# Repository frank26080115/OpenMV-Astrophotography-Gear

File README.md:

I made a Polar Scope and Autoguider using OpenMV. Both projects utilize OpenMV's embedded image processing algorithms to assist in astrophotography while using WiFi to provide a user interface on any smartphone.

A polar scope is a small telescope used to polar-align star-tracking camera mounts and equatorial telescope mounts. A digital camera version that leverages OpenMV computer vision algorithms can achieve much better accuracy, improving the quality of astro-photographs! With a WiFi connected web UI, it's way more convenient to use.

An autoguider is something that locks onto one star, and commands a computerized telescope mount to move in tiny steps to follow that one star, thus correcting for any errors in the gear train and polar alignment. This prevents blurriness in astrophotographs in extra long exposures.

OpenMV is an open source hardware platform that combines a camera, microcontroller, and image processing algorithms. It can run MicroPython and has accessories such as the WiFi shield. It is a quick and easy way to implement low power embedded vision processing in projects such as self-driving robot racecars.

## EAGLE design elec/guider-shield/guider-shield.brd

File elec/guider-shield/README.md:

This circuit schematic and PCB design is a variation of the OpenMV WiFi shield.

The original GitHub repo for the OpenMV WiFi shield is found at [https://github.com/openmv/openmv-boards/tree/master/shields/wifi](https://github.com/openmv/openmv-boards/tree/master/shields/wifi)

It allows for a bigger camera lens to be mounted. It also adds a ST-4 port in order to control telescope mounts.

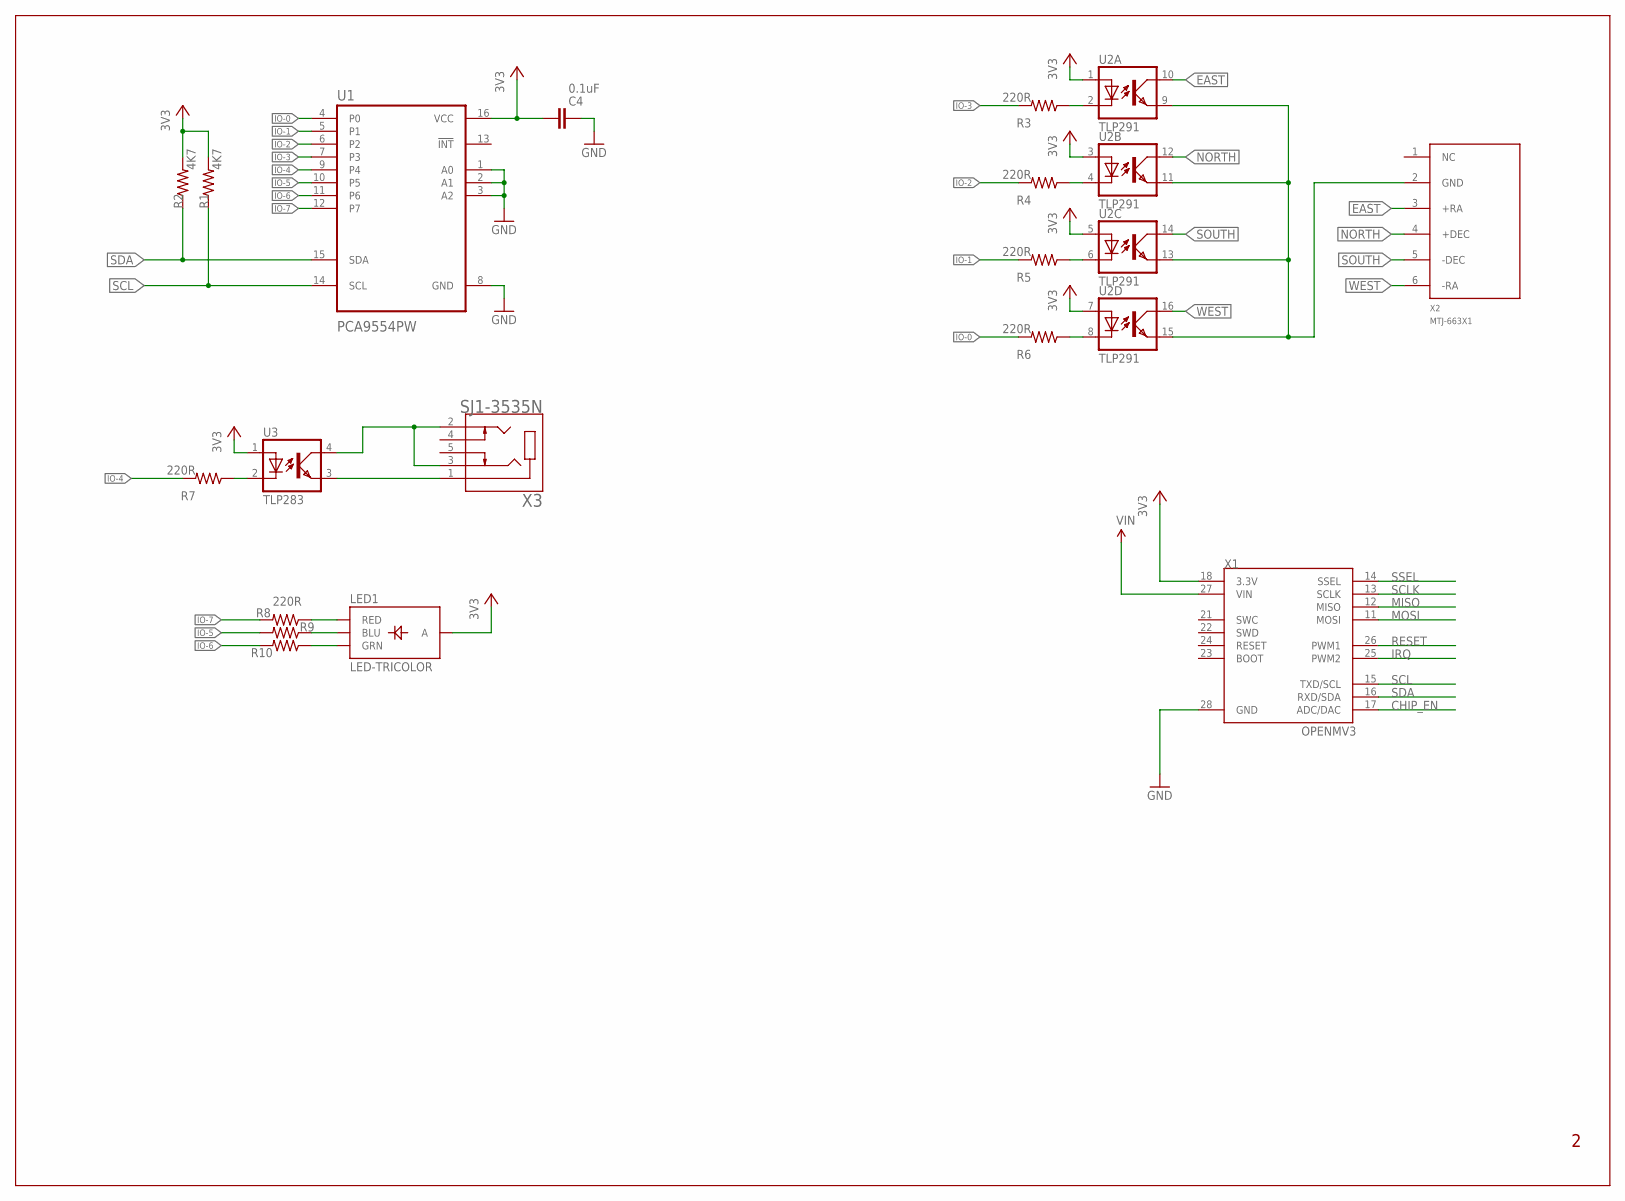
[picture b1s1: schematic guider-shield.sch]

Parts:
C4: 0.1uF; 0603-CAP
LED1: LED-TRICOLOR; LED-TRICOLOR-SMD
R1, R2: 4K7; 0603-RES
R3, R4, R5, R6, R7, R8, R9, R10: 220R; 0603-RES
U1: PCA9554PW; SOP65P640X120-16N
U2: TLP291; SO016
U3: TLP283; MINI-FLAT-4
X1: OPENMV3
X2: MTJ-663X1
X3: SJ1-3535N; CUI_SJ1-3535N

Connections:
3V3: C4.1, LED1.A, R1.2, R2.2, U1.16 (VCC), U2.1 (A), U2.3 (A), U2.5 (A), U2.7 (A), U3.1 (A), X1.18 (3.3V)
CHIP_EN: X1.17 (ADC/DAC)
EAST: U2.10 (COL), X2.3 (+RA)
GND: C4.2, U1.1 (A0), U1.2 (A1), U1.3 (A2), U1.8 (GND), X1.28 (GND)
IO-0: R6.2, U1.4 (P0)
IO-1: R5.2, U1.5 (P1)
IO-2: R4.2, U1.6 (P2)
IO-3: R3.2, U1.7 (P3)
IO-4: R7.2, U1.9 (P4)
IO-5: R9.2, U1.10 (P5)
IO-6: R10.2, U1.11 (P6)
IO-7: R8.2, U1.12 (P7)
IRQ: X1.25 (PWM2)
MISO: X1.12 (MISO)
MOSI: X1.11 (MOSI)
unnamed: LED1.R (RED), R8.1
unnamed: LED1.B (BLU), R9.1
unnamed: LED1.G (GRN), R10.1
unnamed: R3.1, U2.2 (C)
unnamed: R7.1, U3.2 (C)
unnamed: U3.3 (EMIT), X3.1
unnamed: U3.4 (COL), X3.2, X3.3
unnamed: R4.1, U2.4 (C)
unnamed: R5.1, U2.6 (C)
unnamed: R6.1, U2.8 (C)
unnamed: U2.9 (EMIT), U2.11 (EMIT), U2.13 (EMIT), U2.15 (EMIT), X2.2 (GND)
NORTH: U2.12 (COL), X2.4 (+DEC)
RESET: X1.26 (PWM1)
SCL: R1.1, U1.14 (SCL), X1.15 (TXD/SCL)
SCLK: X1.13 (SCLK)
SDA: R2.1, U1.15 (SDA), X1.16 (RXD/SDA)
SOUTH: U2.14 (COL), X2.5 (-DEC)
SSEL: X1.14 (SSEL)
VIN: X1.27 (VIN)
WEST: U2.16 (COL), X2.6 (-RA)

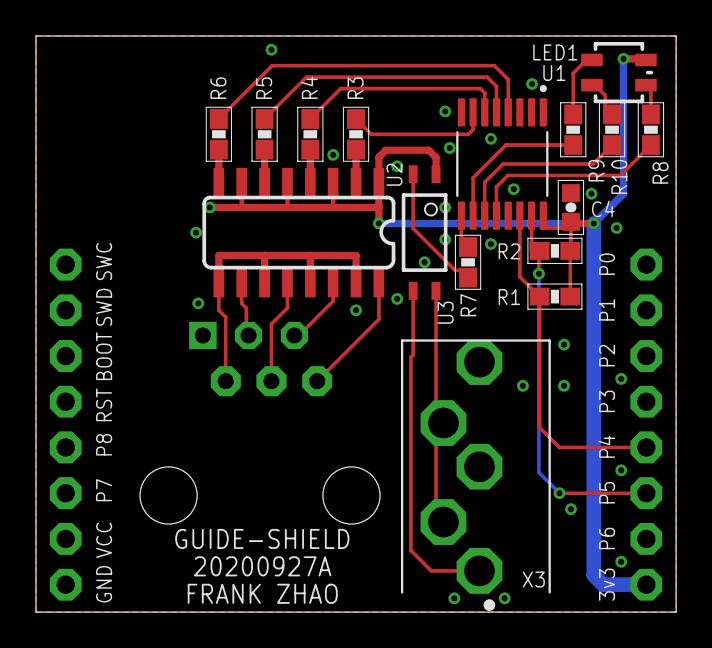
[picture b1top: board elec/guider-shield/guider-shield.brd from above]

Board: 2 copper layers, 35.6 x 32.0 mm, 18 parts (1 on the bottom side), 27 nets.

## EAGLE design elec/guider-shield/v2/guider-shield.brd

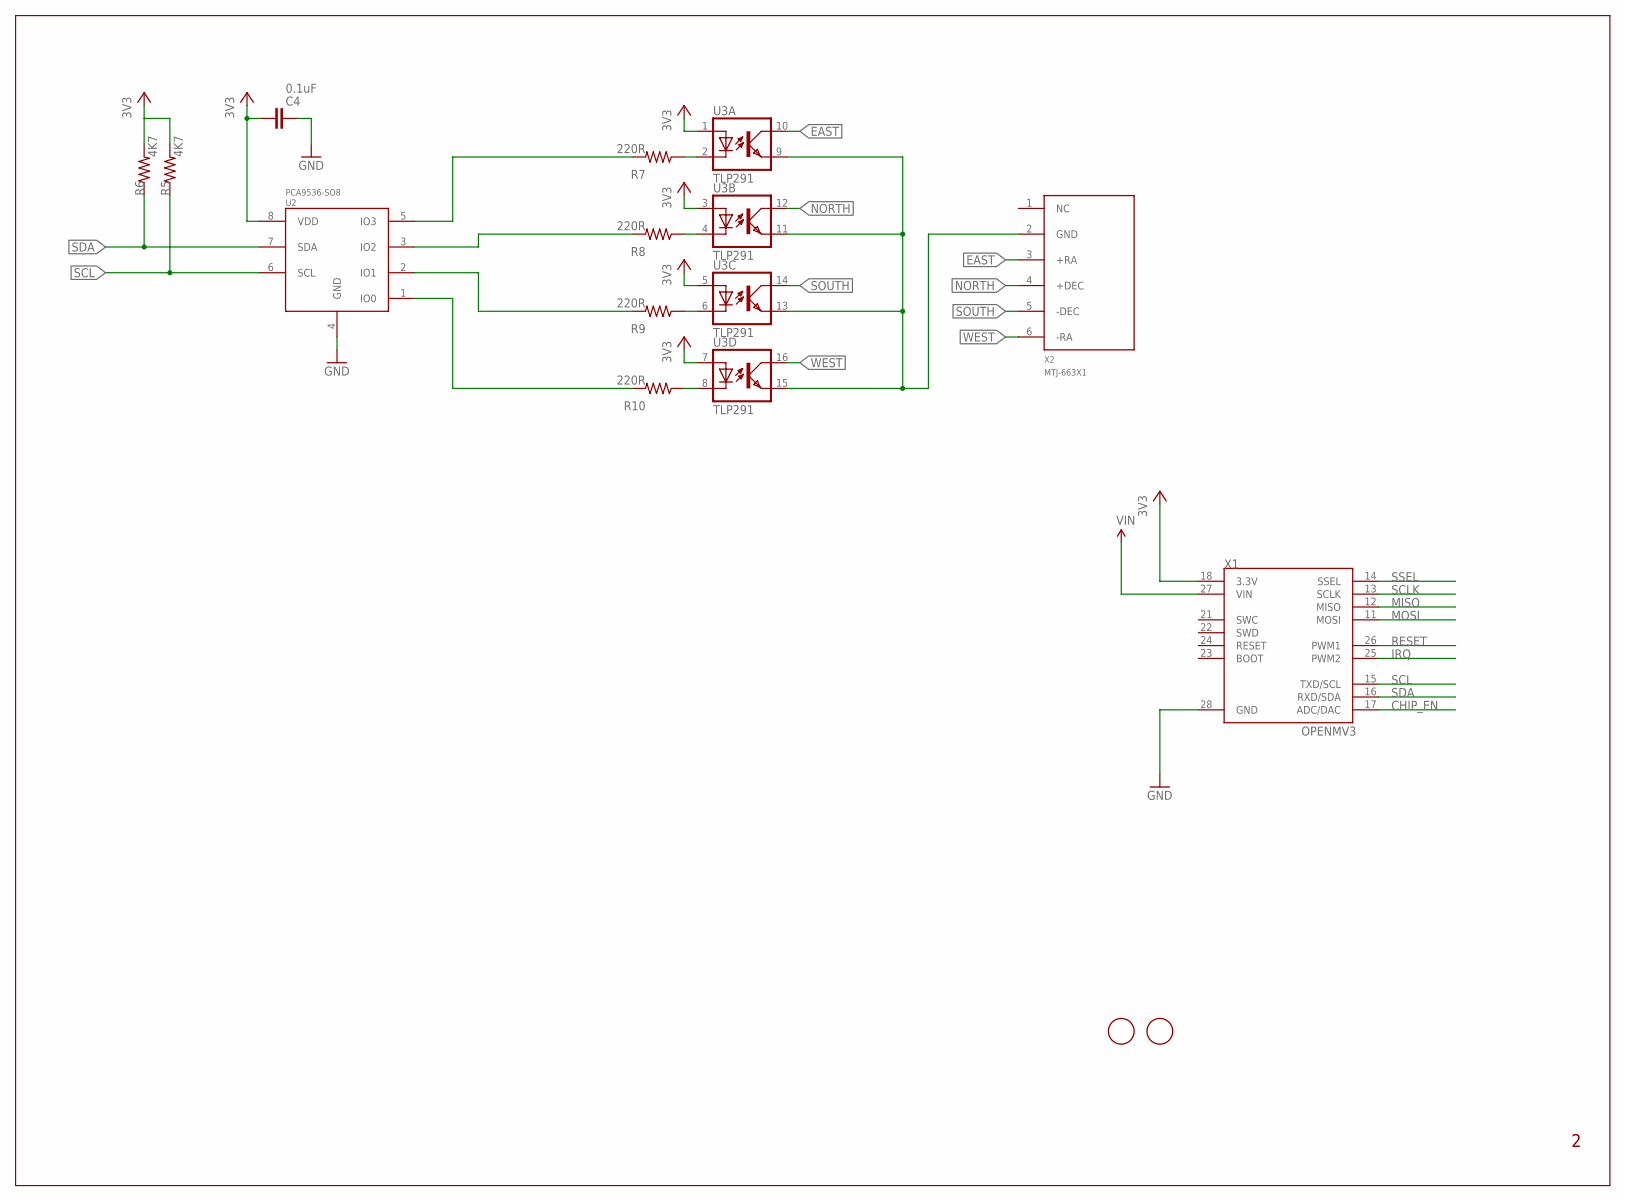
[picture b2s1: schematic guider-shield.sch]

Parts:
C4: 0.1uF; 0603-CAP
R5, R6: 4K7; 0603-RES
R7, R8, R9, R10: 220R; 0603-RES
U2: PCA9536-SO8; SO08
U3: TLP291; SO016
U$1, U$2: FIDUCIAL; FIDUCIAL_1MM
X1: OPENMV3
X2: MTJ-663X1

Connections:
3V3: C4.1, R5.2, R6.2, U2.8 (VDD), U3.1 (A), U3.3 (A), U3.5 (A), U3.7 (A), X1.18 (3.3V)
CHIP_EN: X1.17 (ADC/DAC)
EAST: U3.10 (COL), X2.3 (+RA)
GND: C4.2, U2.4 (GND), X1.28 (GND)
IRQ: X1.25 (PWM2)
MISO: X1.12 (MISO)
MOSI: X1.11 (MOSI)
unnamed: R7.2, U2.5 (IO3)
unnamed: R8.2, U2.3 (IO2)
unnamed: R7.1, U3.2 (C)
unnamed: R8.1, U3.4 (C)
unnamed: R9.1, U3.6 (C)
unnamed: R10.1, U3.8 (C)
unnamed: R9.2, U2.2 (IO1)
unnamed: R10.2, U2.1 (IO0)
unnamed: U3.9 (EMIT), U3.11 (EMIT), U3.13 (EMIT), U3.15 (EMIT), X2.2 (GND)
NORTH: U3.12 (COL), X2.4 (+DEC)
RESET: X1.26 (PWM1)
SCL: R5.1, U2.6 (SCL), X1.15 (TXD/SCL)
SCLK: X1.13 (SCLK)
SDA: R6.1, U2.7 (SDA), X1.16 (RXD/SDA)
SOUTH: U3.14 (COL), X2.5 (-DEC)
SSEL: X1.14 (SSEL)
VIN: X1.27 (VIN)
WEST: U3.16 (COL), X2.6 (-RA)

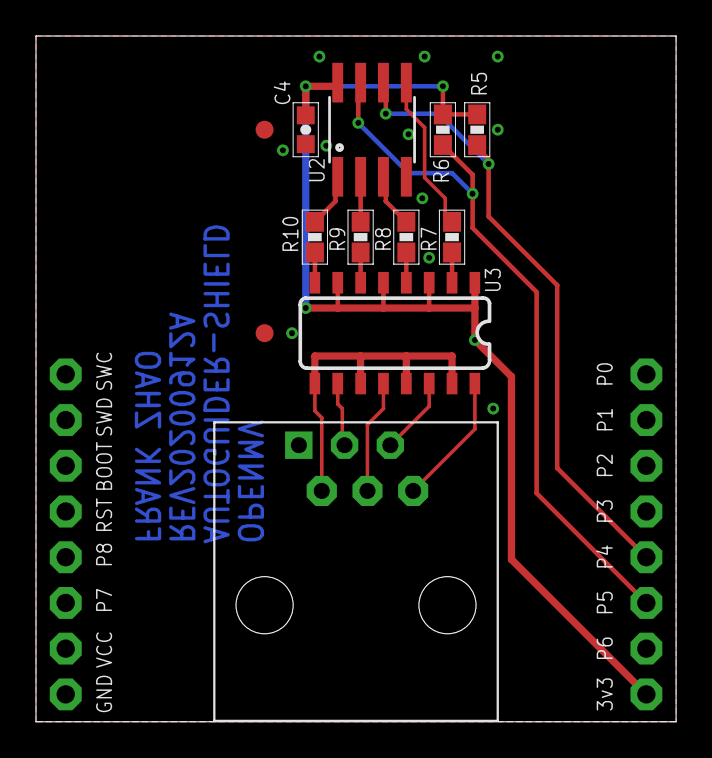
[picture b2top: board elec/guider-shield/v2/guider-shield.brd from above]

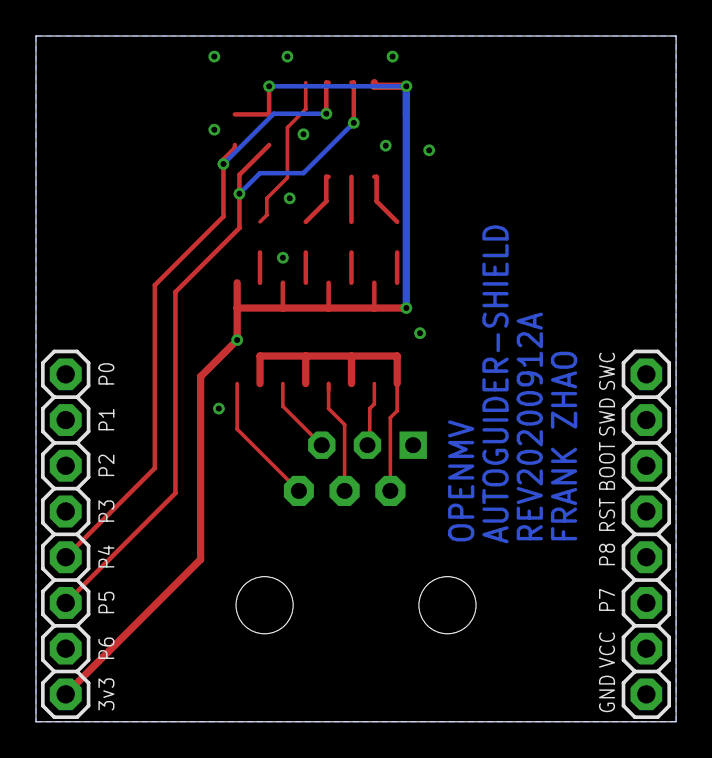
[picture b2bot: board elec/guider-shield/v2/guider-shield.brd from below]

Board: 2 copper layers, 35.6 x 38.1 mm, 14 parts (2 on the bottom side), 17 nets.

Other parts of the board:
U$3: LOGO

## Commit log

2020-08-06 Set theme jekyll-theme-slate
2020-08-10 basic solver working, blob finder working
2020-08-11 captive portal code
2020-08-11 time and location manager
2020-08-12 captiveportal serve files from fs
2020-08-12 create exception logger
2020-08-13 almost done python, facing mem errs
2020-08-13 reduced memory error occurance, and other errs
2020-08-13 polarscope.py minor local var err
2020-08-13 raise exc if from IDE
2020-08-13 fixing bugs
2020-08-13 fixed simulation, fixed solution json obj
2020-08-17 major progress on all features
2020-08-18 major progress, jpg xfer, calib, platesolve, etc
2020-08-19 ui tweaks, more reliable networking, mobile tested
2020-08-21 ui, refraction calc change, level indicator, better hot pixel, better wifi
2020-08-21 renamed the index html file
2020-08-21 platesolver now checks against mystery stars
2020-08-21 optimized platesolver a bit more
2020-08-24 started story documentation
2020-08-24 disabled hot pixel saturation check
2020-08-24 better polaris matching algo, bigger database, reject mystery stars
2020-08-24 better artificial horizon
2020-08-25 documentation update
2020-08-25 removed mention of leap years
2020-08-25 added picture of star adventurer
2020-08-25 changed tracking mount image
2020-08-25 added plate solving screenshot
2020-08-25 minor code clean up
2020-08-25 documentation more images
2020-08-26 removed angle check during calibration
2020-08-26 draw stars that are matched using yellow
2020-08-26 fixed math mistakes in pole solver
2020-08-26 documentation update, add 3D model, add live view video
2020-08-26 plate solving now allows for star clicking
2020-08-26 fixed and polished up calibration
2020-08-27 major documentation update, moved the algorithm description
2020-08-27 click bait
2020-08-27 broken md link
2020-08-27 I don't think GitHub likes image links
2020-08-27 derp file name might be causing problems
2020-08-27 added a blurb about the az eqdist projection
2020-08-27 improved logic about db entries with similar magnitudes
2020-08-27 spell checked
2020-08-27 added database generator scripts
2020-08-28 better clicking of stars
2020-08-28 fixed faulty star size filter
2020-08-28 update db gen to use gnomic projection
2020-08-28 mistakes in math, doesn't work yet
2020-08-28 rever back to my own math, works but shows minor errors
2020-08-29 major update to generic plate solver
2020-08-29 update doc to link new plate solver page
2020-08-29 best plate solver database yet, uses spherical vectors
2020-08-29 added a blurb about nova.astrometry.net
2020-08-30 better plate solver UX, analysis of results
2020-08-30 the halt button now always enabled to clear the selected star
2020-08-30 critical spelling mistake causing missing images
2020-08-30 upload test images
2020-08-30 added mech, added gitignore
2020-08-31 improvements and verification of time calculations
2020-08-31 time acceleration test
2020-08-31 time accel tested the fast mode rotation
2020-08-31 calculations for polaris, and fixed angle bugs while writing
2020-08-31 tweak front page language
2020-08-31 license and instructions
2020-09-01 first rev of guider-shield
2020-09-01 guide-shield almost done
2020-09-01 added animation of Benedikt's algorithm
2020-09-01 guider-shield gerber
2020-09-01 added full screen jpg stream
2020-09-01 better exception loger
2020-09-01 removed numpy
2020-09-03 fixed a bunch of things after outdoor test
    wifi auto reconnect, auto reboot, auto launch soft AP after failed station mode
    wifi hardware fail will now cause a panic
    disabled DNS server
    calibration now has manual overrided
    fixed artificial horizon being 180 flipped
    added camera hardware error warning dialog
2020-09-03 prev fix for rotation missed another required rotation
2020-09-03 cam reliability, non-blocking sensor init
2020-09-03 better UX when changing camera expo settings
2020-09-03 repo name typo woooow
2020-09-04 better openmv image
2020-09-09 advanced calib, low confidence warning
2020-09-10 rename draw_polarscope.js
2020-09-10 explicit js file inclusion
2020-09-11 including a bunch of manuals for telescope mounts
2020-09-11 adding img used in css
2020-09-11 work started on autoguider
2020-09-12 updated guider-shield PCB design
2020-09-24 main startup, fix json long memory crash, avoid amp glow
2020-09-25 UI overhaul prelim
    commonly used functions moved to the top
    removed high speed mode completely
    calibration now automatically detects mode based on number of points saved
    advanced calibration now determines two circles
    LED can be turned off
    default camera exposure changed
2020-09-26 overhaul, cleanup, calib usability, bubble level fixed
2020-09-26 doc update to reflect testing and overhaul of UI
2020-09-29 update documentation about autoguider project
2020-10-02 fw now includes timestamps for images
2020-10-02 guider-shield added intervalometer output
2020-10-02 common functions moved to comutils
2020-10-05 added auto_restart to snapshot_finish
2020-10-08 guider shield v4 gerber sent for fab
2020-10-08 autoguider work in progress
2020-10-21 fixed mistake drawing lines to out-of-view NCP
2020-10-21 fw update to use comutils
2020-10-22 web code now uses websocket
2020-10-24 small restructure of websocket server side code
2021-01-05 forgot to commit comutils
2021-01-06 comutils added refraction and move pt
2021-01-06 untested but inactive code for external OLED and GPS
2021-01-06 polaris_datagen small visual tweak
2021-01-07 work in progress errgraph drawing
2021-01-07 extdisp gps added GPRMC, which has date
2021-01-08 main loop bug fix, captive portal req split bug fix, math utils get time epoch
2021-01-09 made chartist work
2021-01-10 wip added star pointiness analysis
2021-01-10 errgraph test shifted left labels a bit
2021-01-10 test errgraph added legend
2021-01-11 external display tested with hardware
2021-01-11 work in progress, guider calibration, errgraph visual tweaks
2021-01-12 guide calibration bench tested
2021-01-12 guidepulser module in firmware tested
2021-01-13 drawing star profile
2021-01-13 updated firmware fixes long exposure, improves guidepulser
2021-01-13 star list simplifying routing
2021-01-13 star_motion now reports movement object
2021-01-13 autoguider state machine work in progress
2021-01-13 added timing check and test for astro sensor, requires custom FW
2021-01-13 wip commit before updating from master
2021-01-14 star_motion added total multistar mode
2021-01-16 work in progress for autoguider, star_motion multistar corrected logic
2021-01-16 added sensor diagonal size
2021-01-16 backlash mgr uses integers only
2021-01-16 star motion multistar uses weighted average for deltas
2021-01-16 work in progress autoguider state machine
2021-01-17 work in progress on autoguider
2021-01-18 guider calib prep for saving and loading
2021-01-18 added settings parser to comutils
2021-01-18 work in progress for autoguider
2021-01-18 hotpixel encoding and filtering
2021-01-18 attempt to make star json smaller with rounded floats
2021-01-18 work in progress for autoguider, mostly hot pixel related stuff
2021-01-19 improved web server
2021-01-19 new fw, set time for img, pulser get start time and get err
2021-01-19 astro sensor better simulated timing
2021-01-20 fw guidepulser better API
2021-01-20 comment for comutils
2021-01-20 work in progress on autoguider, some simulation tested
2021-01-20 work in progress on autoguider, speed boost in analysis
2021-01-20 work in progress autoguider multistar setting more intuitive
2021-01-20 work in progress autoguider
2021-01-20 adding cftoaster to autoguider
2021-01-21 code to rate clustered stars lower
2021-01-21 dithering is now activated based on dither amount
2021-01-21 work in progress autoguider webpage
2021-01-22 blob accurate centoid now found inside C firmware
2021-01-22 time mgr prevent crash on boot due to fs err
2021-01-22 work in progress autoguider optimization
2021-01-22 autogen SSID now uses uppercase hex
2021-01-23 autoguider motion analysis inside FW in C
2021-01-23 work in progress autoguider, added shutter remaining time, better hw panic
2021-01-23 work in progress autoguider web UI
2021-01-24 autoguider UI work in progress
2021-01-24 autoguider webui auto tx/rx settings, work in progress
2021-01-26 autoguider added split settings for RA and DEC
2021-01-26 added advanced filtering to autoguider, but without web ui
2021-01-26 autoguider removing magic numbers from code
2021-01-27 autoguider, added webui for advflt, added toast, and other work
2021-01-28 autoguider reworked rating calc and auto-star-select
2021-01-28 adding winc fw update attempt code
2021-01-29 autoguider work in progress, added dither calc
2021-01-30 autoguider major work in progress
2021-02-03 autoguider report screen size
2021-02-03 autoguider intervalometer fixed singleshot bug, ui tweaks
2021-02-04 autoguider tweak emojis
2021-02-04 autoguider mobile ui tweaks
2021-02-08 autoguider doc start
2021-02-08 autoguider fixed star max brightness detect
2021-02-08 autoguider doc real star image
2021-02-09 autoguider work in progress, sim calib works
2021-02-10 autoguider wip simulated dithering works
2021-02-10 autoguider added state ignore when button pressed
2021-02-10 autoguider, preemp filt, allowe motion during frame, guideerr graph clear, fixed stop_time=0 bug
2021-02-10 autoguider fixed websock sending stars
2021-02-11 moved a few files to mpy, fixed flip checkbox zeroing out pulses
2021-02-12 autoguider doc work in progress
2021-02-14 added polarscope usage animation
2021-02-14 fixed polarscope manual calibration not working from web ui
2021-02-14 update project status in documentation
2021-02-15 Set theme jekyll-theme-leap-day
2021-02-15 doc changes for new theme
2021-02-15 documentation index retarget
2021-02-15 doc removed title from index
2021-02-15 md links don't work
2021-02-15 doc updated polar scope instructions
2021-02-15 autoguider webui, incorrect var name causing error
2021-02-16 additions to documentation
2021-02-16 doc added stacking and dithering
2021-02-16 main readme urls now goes to github io
2021-02-16 changes to dithering doc and imgs
2021-02-16 doc intro page changes
2021-02-16 PHD2 error graph comparison image edit
2021-02-16 update autoguider webpage documentation
2021-02-17 removed old guidescope images
2021-02-17 autoguider slow coord corrections after dithering disable
2021-02-17 add 2 autoguider sample frames
2021-02-17 doc navigation improvements, added custom css for theme
2021-02-17 added clickable title to doc
2021-02-17 tweaked documentation
2021-02-17 doc template never use page title, always site title
2021-02-17 added sample autoguider image to documentation
2021-02-17 polar scope web page nav bar looked weird
2021-02-17 attempt to make doc nav bar must have more than 1
2021-02-17 added pic of autoguider on redcat
2021-02-17 automatic main.py startup file
2021-02-18 openmv firmware snapshot
2021-02-18 updated fw, and a lot of bug fixes
2021-07-21 spelling mistake

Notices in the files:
elec/guider-shield/v1/guider-shield.sch:
Copyright (c) 2013 Ibrahim Abd Elkader
This work is licensed under the Creative Commons Attribution-ShareAlike 3.0 License.
To view a copy of this license, visit http://creativecommons.org/licenses/by-sa/3.0
